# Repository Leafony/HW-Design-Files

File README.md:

# License

These files are licensed under a [Creative Commons Attribution license(CC-BY)](https://creativecommons.org/licenses/by/4.0/).

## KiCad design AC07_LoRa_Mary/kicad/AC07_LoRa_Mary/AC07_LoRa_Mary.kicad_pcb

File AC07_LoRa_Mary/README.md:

# FP-10/C-Flashを使ったFWの書き込み方
## はじめに
本内容は、AC07 LoRa MaryにFP-10/C-Flashを使ったFWの書き込み方を記します。
## 用意するもの
### LoRa Mary AS
* AC07 LoRa Mary
* AX01 Shield
* AX02 29 pin
* AZ01 USB
* Z63 Nut Plate
* M2X8mm ネジ
### その他
* FP-10
* リーフ組立て治具(Leafx3)
* USBケーブル(mini USBと micro USBの2種類)
* ACアダプター
* PC  [^1]
[^1]:FP-10へプログラムを書き込む時だけ必要で、LoRa Maryへの書き込み時は不要
## FP-10へプログラムの書き込み
* FP-10をPCに繋ぎ、C-Flashを立ち上げます。
* 設定→ターゲット設定をクリックします。
* 次に、マイコンを絞るこむため、メーカ名を指定し、フィルタはSTM32L07xxZを選択し、起動するをクリックします。
* 初期設定のタグで、ターゲットを未接続、インターフェースはSWD、1MHzを選択します。
* ファイル→ロード→追加をクリックし、v1.2.3のbinファイルを指定します。
* Flash開始アドレスは 0x08000000 なので、ロード・アドレスを0x08000000にします。
* データ→書き込みで、FP-10へプログラムを書き込みます。
## 組立て

|Stack No| Leaf | 
| :---  | :--- | 
|1 | AX02 29 pin |
|2|  AC07 LoRa Mary| 
|3|  AX01 Shield| 
* **29 pinのコネクタは、外して使用します。**
* USBリーフは、LoRa Maryに電源を供給するために使用します。
* SWCコネクタ1pin(赤)は、[こちら](https://docs.leafony.com/docs/environment/stm32/stm32_debug/#%E6%8E%A5%E7%B6%9A%E6%96%B9%E6%B3%95)を参照願います。 
## LoRa Maryへの書き込み
* FP-10をAC アダプターに接続します。
* LoRa MaryとUSBをShieldにネジ止めし、AC アダプターに接続します。
* ShieldのSWDにFP-10を繋げます。
* FP-10のPROGRAMボタンをクリックします。STSのLEDが約10秒間点滅し、ピーと音がなり、点灯に変われば、OKです。

# LoRa Mary/AV06 1.8V～5.5V 検査手順
## はじめに
本内容は、LoRa MaryとAV06 1.8V～5.5Vを同時に検査する手順を記します。
## 用意するもの
### LoRa Mary/AV06 1.8V～5.5V AS
* AP03 STM32 MCU
* AC07 LoRa Mary[^2]
* AI01 4-Sensors
* AV06 1.8V～5.5V[^2]
* AX03 Leaf x2
* [2.54x6P through hole](https://github.com/Leafony/HW-Design-Files/tree/master/2.54x6P_through_hole)　6p-SHコネクタ・ケーブル付き
* AZ63 Nut Plate
* M2X14mm ネジ
[^2]:検査対象のリーフ
### Solar-charger-debugger AS
* [Solar-charger-debugger-Leaf](https://github.com/Leafony/HW-Design-Files/tree/master/Solar-charger-debugger-Leaf) [^3]
* AZ01 USB
* AZ63 Nut Plate
* M2X8mm ネジ
* USケーブル 
[^3]:Solar-charger-debugger-Leafは、高さ約3mmなので必ず上段にします。
### その他
* PC
* テスター
* リーフ組立て治具(Leafx3)
* PHコネクタ付き単３x３本電池ボックス

## ソースコード
* [STM32_LoRa_4-Sensors_Transmitter](https://github.com/Leafony/Sample-Sketches/tree/master/STM32_LoRa_4-Sensors_Transmitter)
## 組立て

**LoRa Mary/1.8V～5.5V AS**</br>

* AX03 Leaf x2の右側のコネクタは、外して使用します。 

|Stack No| Left Side Leaf| Right Side Leaf |
| :---:  | :--- | :--- |
|1 |   AI01 4-Sensors | － |
|2|  [2.54x6P through hole](https://github.com/Leafony/HW-Design-Files/tree/master/2.54x6P_through_hole) | － | 
|3|  AX03 Leaf x2 | AX03 Leaf x2| 
|4|  AP03 STM32 MCU | AC07 LoRa Mary| 
|5|  － | AV06 1.8V～5.5V| 

**Solar-charger-debugger AS**</br>

|Stack No| Leaf | 
| :---  | :--- | 
|1 |   [Solar-charger-debugger-Leaf](https://github.com/Leafony/HW-Design-Files/tree/master/Solar-charger-debugger-Leaf) |
|2|  AZ01 USB| 
## 検査方法
1.Solar-charger-debuggerをRunモードにします。

2.Solar-charger-debugger-Leafにテスターを当て、3.3V±0.3Vを確認します。（**初回のみ、2回目以降は省略**)
 
3.Arduino IDEのシリアルモニタを開き、ボーレートを115200bpsにします。[^3]
[^3]:Arduino IDEの設定に関して、[こちら](https://docs.leafony.com/docs/environment/stm32/arduino_ide/)を参照願います。

4.STM32 MCUの[リセットスイッチ](https://docs.leafony.com/docs/environment/stm32/arduino_ide/#%E3%83%9E%E3%82%A4%E3%82%B3%E3%83%B3%E3%83%9C%E3%83%BC%E3%83%89%E3%81%AE%E5%8B%95%E4%BD%9C%E7%A2%BA%E8%AA%8D)を押すと、以下のように表示出来ればOKです。

```
Starting LoRa 4-Sensors Transmitter...
Initializing sensors...
Sensors initialized.
Successfully started!
Sending packet... 
Wakeup Sensors.
3.89V,30.97℃,49.99%,181.60lx,0.05g,0.03g,0.97g
end!
```
## 同軸コネクタの導通チェック
1.A点と同軸コネクタのSIGNAL部分にテスターをあて、導通を確認します。

2.A点とGND部分にテスターをあて、ショートしていないか確認します。

# 外部アンテナの電波強度測定
## はじめに
本内容は、外部アンテナの電波強度の測定方法を記します。送信側は`LoRa Mary/1.8V～5.5V 検査手順検査`で使用したセットを使い、受信側は新たに用意します。

## 用意するもの

### LoRa Mary RX AS
* AP03 STM32 MCU
* AC07 LoRa Mary
* AX04 Spacer
* AX03 Leaf x2
* AZ01 USB
* FPC antenna(1018-504B)　

### LoRa Mary　TX AS
`LoRa Mary/1.8V～5.5V 検査手順検査`で使用したセットを使用します。

### その他
* PC
* リーフ組立て治具(Leafx3)
* アクリル台 
* USBケーブル

## アンテナの切替
LoRa Maryは、内蔵しているChipアンテナがデフォルトの設定になっています。今回は、外部アンテナを使用するため、0Ω抵抗を付け替えます。[こちら](https://docs.leafony.com/docs/leaf/communication/ac07/#%E5%A4%96%E8%A6%B3)を参照願います。

## RXのソースコード
* [STM32_LoRa_Receiver_LCD](https://github.com/Leafony/Sample-Sketches/tree/master/STM32_LoRa_Receiver_LCD))

## 組立て

**LoRa Mary RX AS**</br>
* AX03 Leaf x2の右側のコネクタは、外して使用します。 
* FPC antenna をアクリルに貼り付けて、測定してください。
* FPC antenna のコネクタが干渉するので、AX04 Spacerリーフは必ず付けてください。

|Stack No| Left Side Leaf| Right Side Leaf |
| :---:  | :--- | :--- |
|1 |    AP03 STM32 MCU| － |
|2|  AX03 Leaf x2 | AX03 Leaf x2| 
|3| AZ01 USB|AX04 Spacer | 
|4|  － | AC07 LoRa Mary | 

## 検査方法
1.送信側のプログラムを実行させ、電波を飛ばします。[^4]

[^4]:電池で駆動させるだけで、パソコンでと接続する必要は有りません。

2.受信側(LoRa Mary RX AS)をUSBケーブルでパソコンと接続します。

2.Arduino IDEのシリアルモニタを開き、ボーレートを115200bpsにします。[^3]
[^3]:Arduino IDEの設定に関して、[こちら](https://docs.leafony.com/docs/environment/stm32/arduino_ide/)を参照願います。

4.STM32 MCUの[リセットスイッチ](https://docs.leafony.com/docs/environment/stm32/arduino_ide/#%E3%83%9E%E3%82%A4%E3%82%B3%E3%83%B3%E3%83%9C%E3%83%BC%E3%83%89%E3%81%AE%E5%8B%95%E4%BD%9C%E7%A2%BA%E8%AA%8D)を押すと、以下のように表示され、電波強度(RSSI)が測定出来ます。

```
======================
=== Received Packet ===
Message: 3.97V,24.03℃,100.00%,146.08lx,-0.33g,-0.93g,0.27g
RSSI: -55 dBm
=======================
```
5.アンテナの向き、距離、金属の有無で、電波性能は大きく異なります。比較をする場合は、条件を揃えて電波強度を測定します。

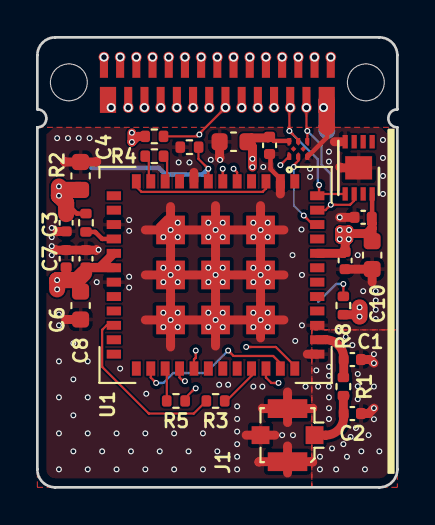
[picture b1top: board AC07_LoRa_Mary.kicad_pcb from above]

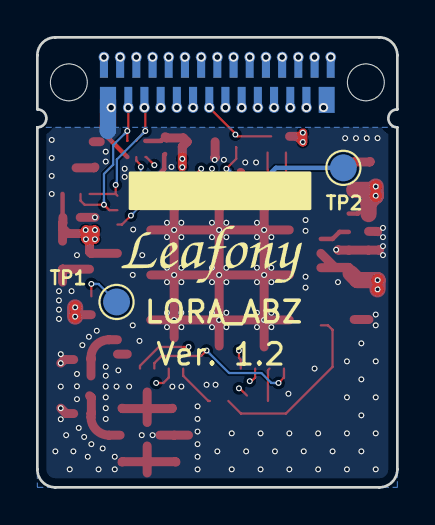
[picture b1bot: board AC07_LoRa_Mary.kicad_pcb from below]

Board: 4 copper layers, 20.0 x 25.0 mm, 28 parts (3 on the bottom side), 22 nets.

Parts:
C1, C2: DNP; C_0402_1005Metric
C3, C6, C9, C11: 100n; C_0402_1005Metric
C4, C8, C10, C12: 10u; C_0603_1608Metric
C5, C7: 1u; C_0402_1005Metric
CN1: Leafony Bus; CN_F29_B29
J1: Conn_Coaxial; U.FL_Molex_MCRF_73412-0110_Vertical
LOGO1: LOGO; LEAFONY_LOGO
R1, R2, R3, R4: 0R; R_0402_1005Metric
R5: DNP; R_0402_1005Metric
R6, R8, R9: 1M; R_0402_1005Metric
TP1, TP2: TestPoint; TestPoint_Pad_D1.5mm
U1: CMWX1ZZABZ-091; CMWX1ZZABZ
U2: ATECC608A-MAHDA; DFN-8-1EP_3x2mm_P0.5mm_EP1.3x1.5mm
U3: TCA9536ADTMR; X2SON8_DTM_TEX

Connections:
+3V3: C3.1, C4.1, C5.1, C6.1, C7.1, C8.1, C9.1, C10.1, C11.1, C12.1, CN1.B1 (3.3V), CN1.F1 (3.3V), R2.2, R6.2, R8.2, U1.5 (VDD_MCU), U1.6 (VDD_RF), U1.32 (VREF+), U2.8 (VCC), U3.7 (VCC)
/LORA_BOOT0: R9.2, TP2.1, U1.43 (BOOT0), U3.1 (P0)
/LORA_MISO: CN1.B19 (D12), CN1.F19 (D12), R5.1, U1.24 (PA2/ADC2)
/LORA_MOSI: CN1.B17 (D11), CN1.F17 (D11), U1.14 (PB15/SPI2_MOSI), U1.23 (PA3/ADC3)
/LORA_NRES: R8.1, TP1.1, U1.34 (~MCU_RST), U3.2
/LORA_RF_IRQ: CN1.B28 (D5), CN1.F28 (D5), U1.22 (PA4/ADC4/DAC1)
/LORA_SCK: CN1.B21 (D13), CN1.F21 (D13), U1.16 (PB13/SPI2_SCK)
/LORA_SSN: CN1.B15 (D10), CN1.F15 (D10), R6.1, U1.17 (PB12/SPI2_NSS)
/SCL: CN1.B25 (SCL), CN1.F25 (SCL), U1.35 (PB8/I2C1_SCL), U2.6 (SCL), U3.5 (SCL)
/SDA: CN1.B23 (SDA), CN1.F23 (SDA), U1.36 (PB9/I2C1_SDA), U2.5 (SDA), U3.6 (SDA)
/SWCLK: CN1.B29 (SWCLK), CN1.F29 (SWCLK), U1.42 (PA14/SWCLK)
/SWDIO: CN1.B2 (SWDIO), CN1.F2 (SWDIO), U1.41 (PA13/SWDIO)
GND: C1.2, C2.2, C3.2, C4.2, C5.2, C6.2, C7.2, C8.2, C9.2, C10.2, C11.2, C12.2, CN1.B27 (GND), CN1.F27 (GND), J1.2 (Ext), R9.1, U1.3 (GND), U1.7 (GND), U1.25 (GND), U1.27 (GND), U1.38 (PB7/LPTIM1_IN2), U1.44 (GND), U1.49 (GND), U1.50 (GND), U1.51 (GND), U1.52 (GND), U1.53 (GND), U1.54 (GND), U1.55 (GND), U1.56 (GND), U1.57 (GND), U2.4 (GND), U2.9 (EP), U3.3 (GND)
unnamed: C2.1, J1.1 (In), R1.2
unnamed: C1.1, R1.1, U1.26 (ANT)
unnamed: R3.2, U1.21 (PA5/ADC5/DAC2)
unnamed: U1.39 (PB6/LPTIM1_ETR), U1.48 (VDD_TCXO)
unnamed: R5.2, U1.15 (PB14/SPI2_MISO)
unnamed: R4.2, U1.46 (PH0/OSC_IN)
unnamed: R3.1, U1.10 (SX1276_DIO4)
unnamed: R4.1, U1.47 (TCXO_OUT)
unnamed: R2.1, U1.4 (VDD_USB)

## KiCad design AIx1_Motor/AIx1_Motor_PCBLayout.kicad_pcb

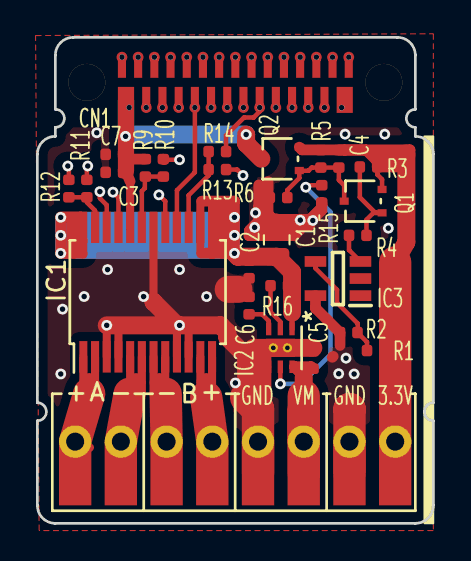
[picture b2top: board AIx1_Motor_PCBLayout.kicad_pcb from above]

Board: 4 copper layers, 22.0 x 27.0 mm, 35 parts (0 on the bottom side), 45 nets.

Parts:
C1: 10uF 25V 2012; C_0805_2012Metric
C2, C3, C4: 0.1uF 50V 1005; C_0402_1005Metric
C5, C7: 1uF 25V 1005; C_0402_1005Metric
C6: 10nF 50V 1005; C_0402_1005Metric
CN1: Leafony bus; CN_F29_B29
IC1: TB6612FNG; SSOP-24_5.3x8.2mm_P0.65mm
IC2: TPS22810DRVT
IC3: LMV431ACM5_NOPB; SOT95P280X145-5N
Q1, Q2: SSM3J132TU_LF
R1: 300k(F); R_0402_1005Metric
R2: 82k(F); R_0402_1005Metric
R3: 4.7k(F); R_0402_1005Metric
R4: 22k(F); R_0402_1005Metric
R5, R6: 1M (F); R_0402_1005Metric
R9, R12, R14: NM; R_0402_1005Metric
R10, R11, R13: 0; R_0402_1005Metric
R15: 100k(J); R_0402_1005Metric
R16: 3.3k(J); R_0402_1005Metric
TP1, TP2, TP3, TP4, TP5, TP6, TP7, TP8: TestPoint; TEST-POINT-CRCLE

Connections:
+3V3: C3.1, C7.1, CN1.B1, CN1.F1, IC1.20, Q2.3, R9.1
+VM: C1.1, C2.1, IC1.13, IC1.14, IC1.24, IC2.1, R16.1
/3.3VIN: C4.1, Q1.2, Q2.2, R1.1, R3.1, R5.1, TP8.1
/A0: CN1.B6, CN1.F6
/A1: CN1.B8, CN1.F8
/A2: CN1.B10, CN1.F10
/A3: CN1.B12, CN1.F12
/A4: CN1.B14, CN1.F14
/A5: CN1.B16, CN1.F16
/AO1: IC1.1, IC1.2, TP1.1
/AO2: IC1.5, IC1.6, TP2.1
/AREF: CN1.B4, CN1.F4
/BO1: IC1.11, IC1.12, TP4.1
/BO2: IC1.7, IC1.8, TP3.1
/D0: CN1.B18, CN1.F18
/D1: CN1.B20, CN1.F20
/D2: CN1.B22, CN1.F22
/D3: CN1.B24, CN1.F24, IC2.5, R10.1, R15.1
/D4: CN1.B26, CN1.F26, IC1.22
/D5: CN1.B28, CN1.F28, R11.1
/D6: CN1.B7, CN1.F7, R13.1
/D7: CN1.B9, CN1.F9, IC1.16
/D8: CN1.B11, CN1.F11
/D9: CN1.B13, CN1.F13
/D10: CN1.B15, CN1.F15, R12.1
/D11: CN1.B17, CN1.F17, R14.1
/D12: CN1.B19, CN1.F19, IC1.21
/D13: CN1.B21, CN1.F21, IC1.17
/PWMA: IC1.23, R11.2, R12.2
/PWMB: IC1.15, R13.2, R14.2
/RESET: CN1.B5, CN1.F5
/SCL: CN1.B25, CN1.F25
/SDA: CN1.B23, CN1.F23
/STBY: IC1.19, R9.2, R10.2
/SWCLK: CN1.B29, CN1.F29
/SWDIO: CN1.B2, CN1.F2
/VBUS: CN1.B3, CN1.F3
/VMIN: C5.1, IC2.6, TP6.1
GND: C1.2, C2.2, C3.2, C5.2, C6.2, C7.2, CN1.B27, CN1.F27, IC1.3, IC1.4, IC1.9, IC1.10, IC1.18, IC2.4, IC2.7, IC3.5, R2.2, R6.2, R15.2, TP5.1, TP7.1
unnamed: C4.2, Q1.3, Q2.1, R5.2, R6.1
unnamed: C6.1, IC2.3
unnamed: IC2.2, R16.2
unnamed: IC3.3, R4.2
unnamed: IC3.4, R1.2, R2.1
unnamed: Q1.1, R3.2, R4.1

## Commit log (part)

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2022-02-03 Add files via upload
    Add resistor(R127)
2024-07-25 add AC07 LoRa Mary
2024-07-25 add AC07 layout & sch pdf
2024-07-25 ドキュメントを追加
2025-02-26 チップアンテナ化に伴う変更
2025-02-26 実装図新規作成
2025-02-26 LTE-M_Maryディレクトリ作成
2025-04-30 スイッチの向き追加

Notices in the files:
parts and their libraries:
Copyright 2016 Accelerated Designs. All rights reserved.
